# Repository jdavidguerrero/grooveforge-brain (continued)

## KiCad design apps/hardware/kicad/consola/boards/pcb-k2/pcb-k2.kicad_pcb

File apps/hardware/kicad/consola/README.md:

# GroovePush — Hardware (KiCad)

Modular hierarchical schematic for the GroovePush controller. See
[ADR-0001](../specs/adr/0001-modular-pcb-topology.md) for the topology decision.

- **Project**: `GroovePush.kicad_pro`
- **KiCad**: v10 (files `version 20260101`)
- **Root sheet**: `GroovePush.kicad_sch` → 4 sub-sheets (one per module / future PCB):
  `processor.kicad_sch`, `encoders.kicad_sch`, `analog.kicad_sch`, `leds.kicad_sch`.

## System topology

```
        ┌────────────────── PROCESSOR BOARD ──────────────────┐
        │  Teensy 4.1 (J1 socket)                              │
 +5V ──▶│  ├─ I2C ─ 2× MCP23017 (U1 0x20 sw, U2 0x21 btn)      │
 PSU  J4│  ├─ 4.7k I2C pull-ups (R1,R2)                        │
        │  └─ decoupling C1/C2/C3                              │
        │   J2      J3       J5/J8      J6        J7      J20   │
        └───┼───────┼─────────┼─────────┼─────────┼───────┼────┘
        I2C │  UART │  ribbon │ ribbon  │  3-wire │ ribbon│
        ┌───▼──┐ ┌──▼───┐ ┌───▼────┐ ┌──▼─────┐ ┌─▼────┐ │ panel
        │Neo-  │ │ RPi5 │ │ENCODER │ │ ANALOG │ │ LED  │ │ buttons
        │Trellis│ │ GUI │ │ board  │ │ board  │ │board │
        └──────┘ └──────┘ └────────┘ └────────┘ └──────┘
```

Each sub-sheet is electrically self-contained and exposes a header — it can become its
own PCB. The inter-board wiring is the **connector contract** in the table below.

## Bill of Materials (initial)

### Processor board (`processor.kicad_sch`)
| Ref | Value | Part | Notes |
|-----|-------|------|-------|
| J1 | Teensy 4.1 socket | 2×24 female header | The Teensy is a module; socket pinout must be mapped to the real Teensy 4.1 footprint before layout |
| U1 | MCP23017 @ 0x20 | I²C 16-bit I/O expander | 8 encoder push-switches (GPA0–6 + GPB0) |
| U2 | MCP23017 @ 0x21 | I²C 16-bit I/O expander | 8 extra panel buttons (GPA0–6 + GPB0) |
| R1, R2 | 4.7 kΩ | I²C pull-ups | SDA / SCL to +3V3 |
| C1, C2 | 100 nF | Decoupling | 1 per MCP23017 |
| C3 | 10 µF | Bulk | +5V rail |
| J2 | 1×4 | NeoTrellis I²C | SDA, SCL, +3V3, GND |
| J3 | 1×4 | RPi5 UART | TX, RX, GND, GND |
| J4 | 1×2 | 5 V power in | +5V, GND |
| J5 | 2×8 | Encoder A/B ribbon | 16 quadrature lines |
| J6 | 1×12 | Analog board | 4 fader + 4 piezo + 2 IR + 3V3 + GND |
| J7 | 1×3 | LED board | LED_DATA, +5V, GND |
| J8 | 1×10 | Encoder switches | 8 switches + GND |
| J20 | 1×10 | Panel buttons | 8 buttons + 2 GND |

### Encoder board (`encoders.kicad_sch`)
| Ref | Value | Part | Notes |
|-----|-------|------|-------|
| RE1–RE8 | EC11 | Rotary encoder + switch | A/B quadrature + push |
| J9 | 2×8 | A/B to processor | mates J5 |
| J10 | 1×10 | Switches to processor | mates J8 |

### Analog board (`analog.kicad_sch`)
| Ref | Value | Part | Notes |
|-----|-------|------|-------|
| RV1–RV4 | ALPS B50K | Slide potentiometer (fader) | wiper → ADC |
| J12–J15 | 1×2 | Piezo element | signal + GND |
| R3–R6 | 1 MΩ | Piezo bleed | across each piezo |
| J16, J17 | 1×3 | Sharp IR sensor | +3V3, GND, OUT |
| J11 | 1×12 | To processor | mates J6 |

### LED board (`leds.kicad_sch`)
| Ref | Value | Part | Notes |
|-----|-------|------|-------|
| U3 | SN74LVC245A | Level shifter 3.3→5 V | data line to strip |
| R7 | 330 Ω | Series | data protection |
| D1 | WS2812B | First pixel (strip = 28) | DIN←data, DOUT→strip |
| C4 | 1000 µF | Bulk | +5V near LEDs |
| C5 | 100 nF | Decoupling | U3 |
| J18 | 1×3 | To LED strip | +5V, DATA, GND |
| J19 | 1×3 | To processor | mates J7 |

### Raspberry Pi 5 accessories (off-board — not on the custom PCB)
> See [ADR-0002](../specs/adr/0002-dual-mode-standalone-direction.md) — direction only,
> for the future **Standalone mode**. These sit on the RPi5's own 40-pin GPIO header, a
> different physical location from the processor board above; no KiCad schematic change.

| Item | Part | Notes |
|---|---|---|
| Audio output | RaspiAudio **Audio+ V2** | HAT DAC, I2S over 40-pin header, 112 dB SNR, 32-bit/384 kHz PCM, 3.5 mm + RCA stereo out. **Output only** (confirmed vs. manufacturer spec — no mic/line input). RPi5-compatible. **In BOM now.** |
| Audio input | RaspiAudio **Mic+** | Planned, not yet acquired. Needed for standalone audio input and any future controller-mode "listen to other instruments" idea. **Not yet in BOM.** |

## Inter-board connector contract

| Processor conn | Mates | Signals | Cable |
|---|---|---|---|
| J2 | NeoTrellis board | I2C_SDA, I2C_SCL, +3V3, GND | 4-wire |
| J3 | Raspberry Pi 5 | TEENSY_TX1→RPi_RX, TEENSY_RX1→RPi_TX, GND, GND | 4-wire (do **not** power the Pi from here) |
| J4 | 5 V PSU | +5V, GND | 5 V / 3 A min |
| J5 ↔ J9 | Encoder board | ENC1..8 A/B (16) | 16-way ribbon |
| J8 ↔ J10 | Encoder board | ENC_SW1..8, GND | 10-way ribbon |
| J6 ↔ J11 | Analog board | FADER1..4, PIEZO1..4, IR1..2, +3V3, GND | 12-way |
| J7 ↔ J19 | LED board | LED_DATA, +5V, GND | 3-wire |
| J20 | Panel buttons | BTN1..8, GND | 10-way |

## Power budget (from `apps/processor/PIN_DISTRIBUTION.md`)
| Rail | Load | Current |
|---|---|---|
| +5V | NeoPixels (28 @ full) | ~1.7 A |
| +5V | Teensy 4.1 | ~0.15 A |
| +3V3 | 2× NeoTrellis, MCP, encoders, sensors | ~0.25 A |
| **Total** | | **5 V / 3 A PSU minimum** |

## Verification status
Connectivity validated via the KiCad MCP net lister (all nets ≥ 2 pins; power rails carry
`PWR_FLAG`; unused MCP/level-shifter pins marked no-connect). Full ERC/netlist export via
`kicad-cli` was **not run in this environment** (no `kicad-cli` on PATH). Open the project
in KiCad 10 and run ERC before layout.

## Known issues / next steps (see `../GAPS_AND_IMPROVEMENTS.md`)
1. **Footprints not yet assigned** — this is schematic-only. Assign before PCB layout.
2. **Teensy socket pin mapping** — J1 pins are logical; map to the real Teensy 4.1
   footprint (verify each GPIO ↔ socket position) before layout.
3. **I2C vs UART NeoTrellis** — this design uses I²C NeoTrellis (0x2E/0x2F) per the user's
   build; the firmware's `UART_CONNECTIONS.md` (NeoTrellis **M4** over UART) is an
   alternative. Reconcile firmware `Config.h` accordingly.
4. **Sharp IR level** — powered from +3V3; select a 3.3 V-compatible rangefinder, or add a
   divider if using a 5 V GP2Y0A part (its output can exceed 3.3 V).
5. **MCP23017 GPA7/GPB7** are output-only (erratum) — intentionally not used as inputs.
6. **Encoder A/B pull-ups** — rely on Teensy internal pull-ups; add external 10 k if noisy.

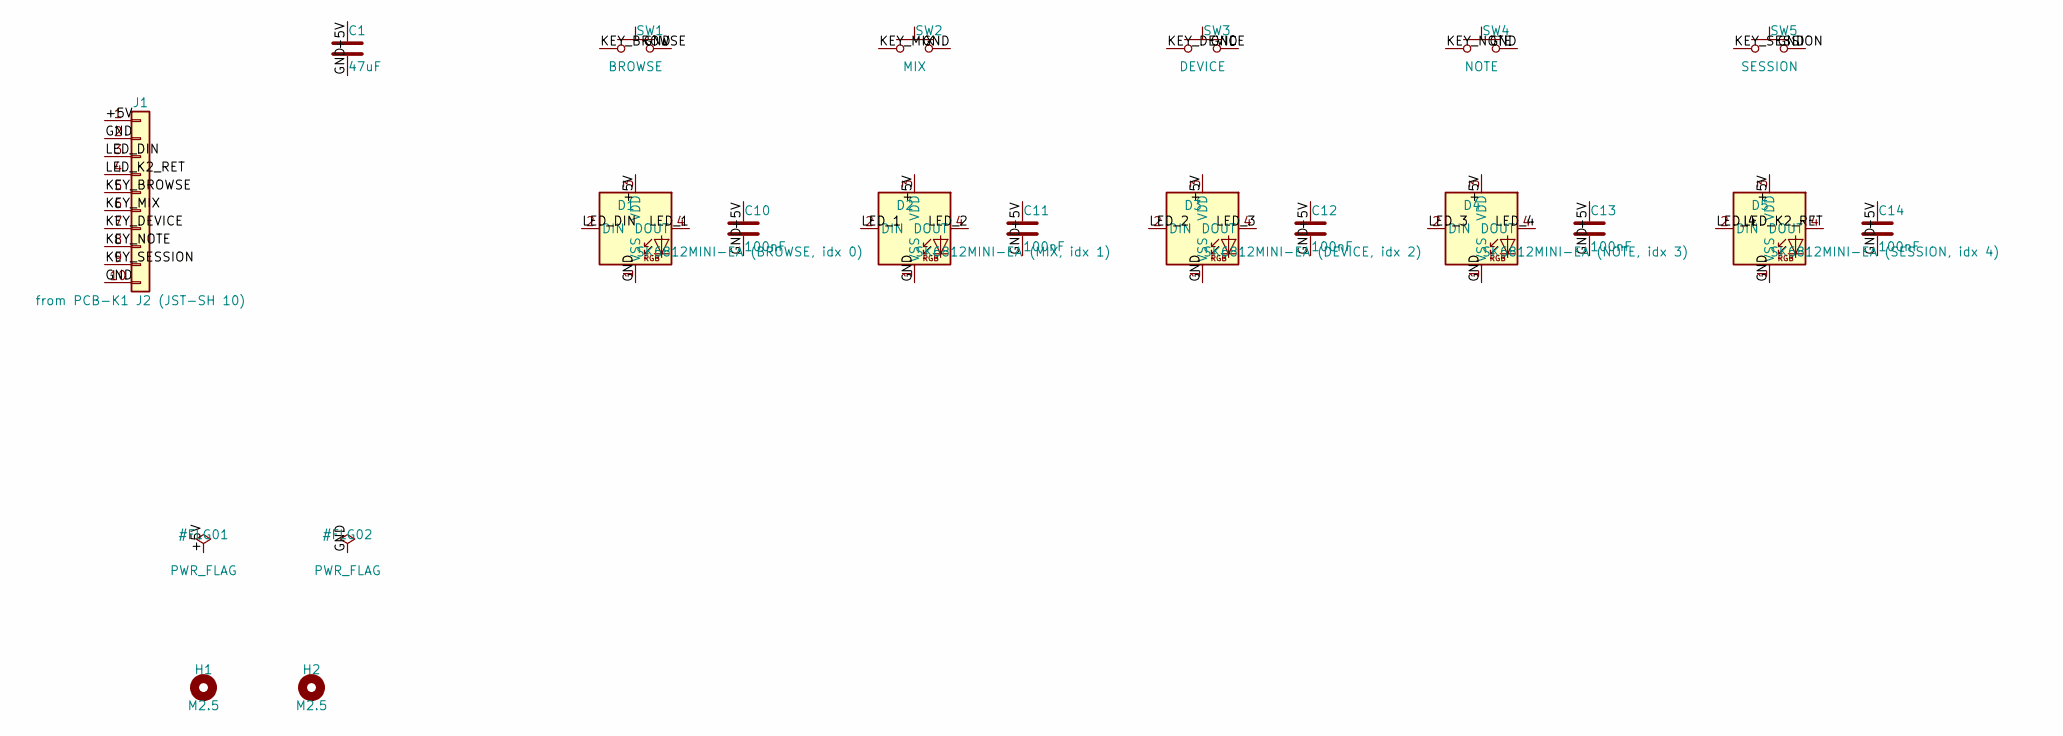
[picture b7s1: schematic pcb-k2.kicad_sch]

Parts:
C1: 47uF; C_1206_3216Metric; LCSC C96123
C10, C11, C12, C13, C14: 100nF; C_0603_1608Metric; LCSC C14663
D1: SK6812MINI-EA (BROWSE, idx 0); LED_SK6812MINI-E_3.2x2.8mm_P1.5mm_ReverseMount; LCSC C5378731
D2: SK6812MINI-EA (MIX, idx 1); LED_SK6812MINI-E_3.2x2.8mm_P1.5mm_ReverseMount; LCSC C5378731
D3: SK6812MINI-EA (DEVICE, idx 2); LED_SK6812MINI-E_3.2x2.8mm_P1.5mm_ReverseMount; LCSC C5378731
D4: SK6812MINI-EA (NOTE, idx 3); LED_SK6812MINI-E_3.2x2.8mm_P1.5mm_ReverseMount; LCSC C5378731
D5: SK6812MINI-EA (SESSION, idx 4); LED_SK6812MINI-E_3.2x2.8mm_P1.5mm_ReverseMount; LCSC C5378731
H1, H2: M2.5; MountingHole_2.7mm_M2.5
J1: from PCB-K1 J2 (JST-SH 10); JST_SH_SM10B-SRSS-TB_1x10-1MP_P1.00mm_Horizontal; LCSC C160409
SW1: BROWSE; SW_Kailh_Choc_V2_1u
SW2: MIX; SW_Kailh_Choc_V2_1u
SW3: DEVICE; SW_Kailh_Choc_V2_1u
SW4: NOTE; SW_Kailh_Choc_V2_1u
SW5: SESSION; SW_Kailh_Choc_V2_1u

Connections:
/+5V: C1.1, C10.1, C11.1, C12.1, C13.1, C14.1, D1.3 (VDD), D2.3 (VDD), D3.3 (VDD), D4.3 (VDD), D5.3 (VDD), J1.1
/GND: C1.2, C10.2, C11.2, C12.2, C13.2, C14.2, D1.1 (VSS), D2.1 (VSS), D3.1 (VSS), D4.1 (VSS), D5.1 (VSS), J1.2, J1.10, SW1.2, SW2.2, SW3.2, SW4.2, SW5.2
/KEY_BROWSE: J1.5, SW1.1
/KEY_DEVICE: J1.7, SW3.1
/KEY_MIX: J1.6, SW2.1
/KEY_NOTE: J1.8, SW4.1
/KEY_SESSION: J1.9, SW5.1
/LED_1: D1.4 (DOUT), D2.2 (DIN)
/LED_2: D2.4 (DOUT), D3.2 (DIN)
/LED_3: D3.4 (DOUT), D4.2 (DIN)
/LED_4: D4.4 (DOUT), D5.2 (DIN)
/LED_DIN: D1.2 (DIN), J1.3
/LED_K2_RET: D5.4 (DOUT), J1.4

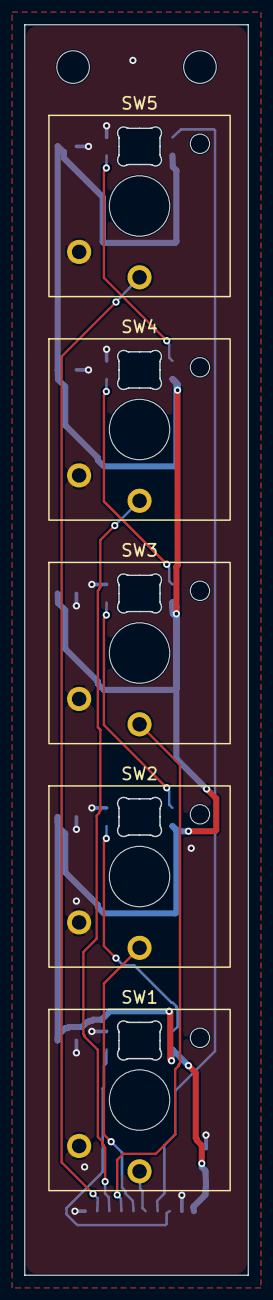
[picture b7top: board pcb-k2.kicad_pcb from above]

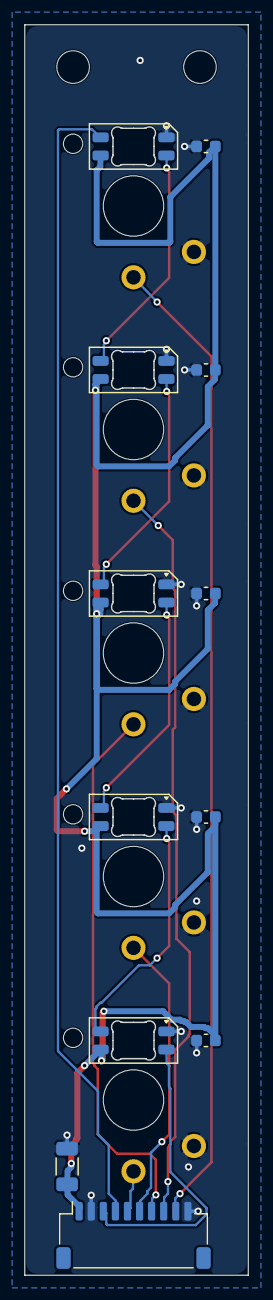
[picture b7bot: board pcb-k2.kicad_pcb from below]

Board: 2 copper layers, 18.5 x 103.5 mm, 19 parts (12 on the bottom side), 13 nets.

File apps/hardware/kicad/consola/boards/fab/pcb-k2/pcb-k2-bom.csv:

Comment,Designator,Footprint,LCSC Part #
47uF,C1,C_1206_3216Metric,C96123
100nF,"C10,C11,C12,C13,C14",C_0603_1608Metric,C14663
SK6812MINI-EA,"D1,D2,D3,D4,D5",LED_SK6812MINI-E_3.2x2.8mm_P1.5mm_ReverseMount,C5378731
SM10B-SRSS-TB,J1,JST_SH_SM10B-SRSS-TB_1x10-1MP_P1.00mm_Horizontal,C160409

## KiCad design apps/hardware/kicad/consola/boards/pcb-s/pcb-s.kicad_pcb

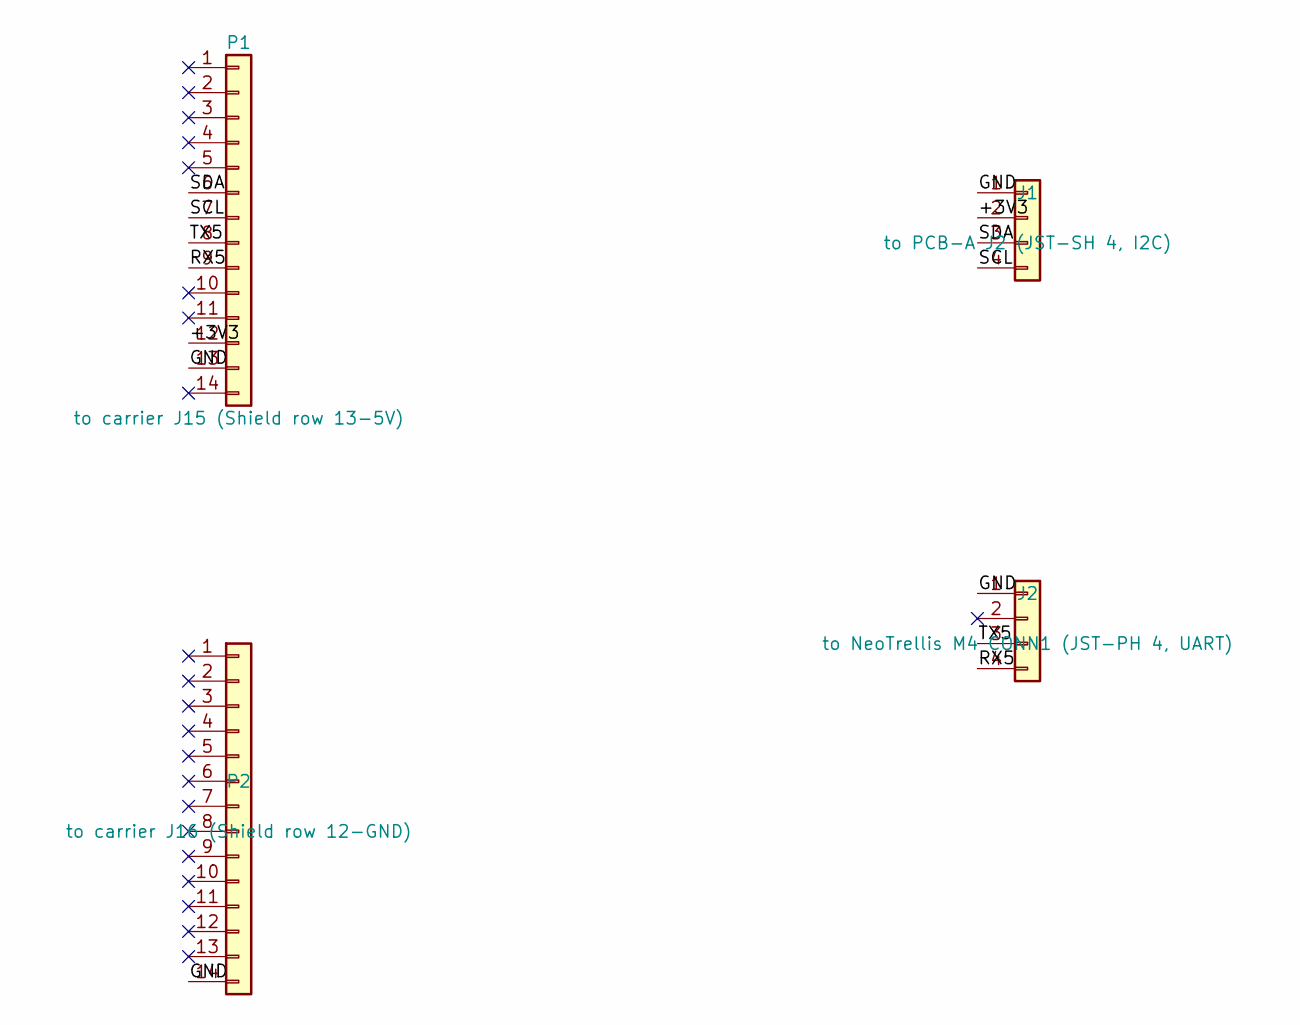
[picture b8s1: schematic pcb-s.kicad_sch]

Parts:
J1: to PCB-A J2 (JST-SH 4, I2C); JST_SH_BM04B-SRSS-TB_1x04-1MP_P1.00mm_Vertical; LCSC C160390
J2: to NeoTrellis M4 CONN1 (JST-PH 4, UART); JST_PH_B4B-PH-K_1x04_P2.00mm_Vertical
P1: to carrier J15 (Shield row 13-5V); PinHeader_1x14_P2.54mm_Vertical
P2: to carrier J16 (Shield row 12-GND); PinHeader_1x14_P2.54mm_Vertical

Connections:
/+3V3: J1.2, P1.12
/GND: J1.1, J2.1, P1.13, P2.14
/RX5: J2.4, P1.9
/SCL: J1.4, P1.7
/SDA: J1.3, P1.6
/TX5: J2.3, P1.8

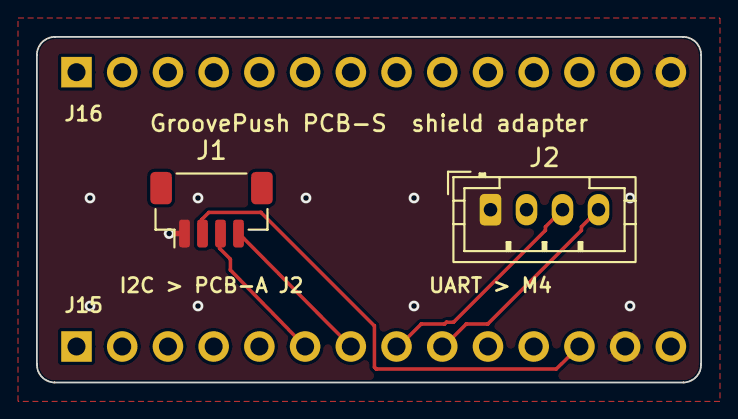
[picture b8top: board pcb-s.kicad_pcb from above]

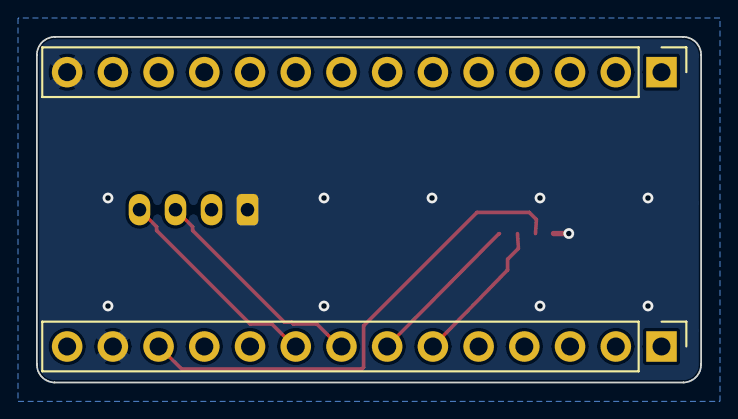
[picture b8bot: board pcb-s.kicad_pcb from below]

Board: 2 copper layers, 36.9 x 19.2 mm, 4 parts (2 on the bottom side), 6 nets.

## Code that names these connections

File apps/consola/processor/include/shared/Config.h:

#pragma once

// === HARDWARE CONFIGURATION ===
// Grid Layout: 8 tracks (columns) × 4 scenes (rows) = 32 pads
#define GRID_TRACKS 8   // 8 tracks (columns) - horizontal
#define GRID_SCENES 4   // 4 scenes (rows) - vertical  
#define TOTAL_KEYS (GRID_TRACKS * GRID_SCENES) // 32 keys total

// Physical NeoTrellis mapping (8x4 orientation)
#define Y_DIM GRID_SCENES // 4 rows (scenes)
#define X_DIM GRID_TRACKS // 8 columns (tracks)
#define I2C_START_ADDR 0x2E // Legacy Seesaw address, unused: the pad grid is a NeoTrellis M4 over UART
// I2C bus = default Wire on Teensy 4.1: SDA=pin 18, SCL=pin 19 -> the two MCP23017 only.
// On the Brain carrier these reach the empty Audio Shield socket J15; the 4.7k pull-ups live on
// the GroovePush adapter, not on the carrier. See PIN_MAP.md.

// === MIDI CONFIGURATION ===
#define SYSEX_START 0xF0
#define SYSEX_END 0xF7
#define MANUFACTURER_ID 0x7F // Universal Non-Commercial (matches Live Remote Script)
#define DEVICE_ID 0x00       // Device channel (matches Live Remote Script)

// === LED BRIGHTNESS ===
#ifdef GF_CONSOLA_S_M4
#define LED_BRIGHTNESS 63
#else
#define LED_BRIGHTNESS 100 // 0-255
#endif
#define NEOPIXEL_PIN 28    // LED chain data: Brain carrier U1 buffer -> R3 -> J5.26 (LED_DIN). See PIN_MAP.md.

// === COLORS (RGB values) ===
#define COLOR_EMPTY 0x202020     // Dim white
#define COLOR_LOADED 0xFF4000    // Orange
#define COLOR_PLAYING 0x00FF00   // Green
#define COLOR_RECORDING 0xFF0000 // Red
#define COLOR_SELECTED 0x0080FF  // Blue
#define COLOR_TRIGGERED 0xFFFF00 // Yellow

// === UART COMMUNICATION ===
// Historical Brain carrier target only (gap G-H10), not consola_uno:
// Consola uses USB to Pi, Serial7 RX28/TX29 to M4; 0/1 are EN_K/EN_A.
//   - Raspberry Pi 5 (GUI): Serial1, pins 0/1, carrier header J6.
//   - NeoTrellis M4 (pads): Serial5, TX5 = pin 20, RX5 = pin 21, via Audio Shield socket J15.
#define TEENSY_GUI_SERIAL Serial1
#define TEENSY_M4_SERIAL  Serial5
#define GUI_BAUD_RATE 115200
// Teensy <-> M4 link: 1 Mbps
#define UART_BAUD_RATE 1000000  // 1 Mbps - Reliable low-latency link
#define UART_BUFFER_SIZE 256
// Heartbeat ping from Teensy to M4
#define UART_PING_INTERVAL_MS 30000     // Send PING every 30 seconds
#define UART_LINK_TIMEOUT_MS 90000      // Consider link down after 90 seconds without RX

// === NEOTRELLIS M4 UART PINS (M4 side: its 4-pin JST port) ===
// Default trellis_m4 Serial1 (SERCOM4); no custom pin mux or bit-banging.
#define UART_RX_PIN 22  // M4 SCL pad, RX from Teensy TX7/29
#define UART_TX_PIN 21  // M4 SDA pad, TX to Teensy RX7/28

// === ABLETON INTEGRATION ===
#define ABLETON_MIDI_CHANNEL 1
#define ABLETON_SYSEX_TIMEOUT 1000

// === DEBUG FLAGS ===
// #define DEBUG_LIVE_LOG  // Enable Live command logging (disabled to reduce spam)

// === FADERS CONFIGURATION (Teensy only) ===
#define NUM_FADERS 4
#define FADER_PINS {A0, A1, A2, A3}  // 4 ALPS B50K faders
#define TRACKS_PER_BANK 4              // Tracks visible per bank (matches fader count)
#define FADER_PICKUP_THRESHOLD 3       // ±3 MIDI units for pickup mode (2.4% tolerance)

// === ENCODERS CONFIGURATION (Teensy only) ===
// Authoritative map: see PIN_MAP.md. All A/B pins come through the Brain carrier's panel
// IDC J5. Kept off Serial1 (0/1, GUI), Serial5 (20/21, M4), I2C (18/19), faders (14-17),
// LED data (28) and pin 13 (onboard LED). Encoder switches are on MCP23017 0x20.
#define NUM_ENCODERS_ACTIVE 4          // Currently wired encoders (build up to 8)
#define NUM_ENCODERS_MAX 8             // Maximum encoders supported
// Format: {Enc1_A, Enc1_B, Enc2_A, Enc2_B, Enc3_A, Enc3_B, Enc4_A, Enc4_B}
#define ENCODER_PINS_ACTIVE {2, 3, 4, 5, 9, 10, 11, 12}
// Encoders 5-8 (Enc5_A,B ... Enc8_A,B)
#define ENCODER_PINS_EXPANSION {22, 24, 26, 30, 31, 32, 34, 35}

// === MCP23017 I/O EXPANDER CONFIGURATION (Teensy only) ===
// Capacity: 16 GPIO/chip, but GPA7/GPB7 are output-only (erratum) -> 14 usable inputs/chip
// max. This build wires 8 pins/chip (GPA0-6 + GPB0), matching hardware/processor.kicad_sch
// exactly (verified via KiCad net lister 2026-07-16). See PIN_MAP.md.
#define MCP_ENCODER_BUTTONS_ADDR 0x20  // MCP23017 #1: encoder push-switches (EC11 integrated)
#define MCP_EXTRA_BUTTONS_ADDR 0x21    // MCP23017 #2: transport/extra buttons
// Interrupt lines (optional, not used by ButtonManager yet): J5.22 / J5.20 on the Brain carrier
#define MCP_ENCODER_BUTTONS_INT_PIN 40
#define MCP_EXTRA_BUTTONS_INT_PIN 41
#define NUM_ENCODER_BUTTONS 8          // 1:1 with the 8 encoders (was wrongly 4 - fixed)
#define NUM_EXTRA_BUTTONS 8            // 4 populated now (Play/Stop/Record/Loop), 4 free
#define TOTAL_MCP_BUTTONS (NUM_ENCODER_BUTTONS + NUM_EXTRA_BUTTONS)  // 16 total wired

// === BUTTON DEBOUNCE ===
#define BUTTON_DEBOUNCE_MS 50

// === ADC CONFIGURATION ===
#define ADC_RESOLUTION 12              // Teensy 4.1 supports 12-bit ADC
#define FADER_TOLERANCE 8              // Minimum change to trigger update (out of 4096)
